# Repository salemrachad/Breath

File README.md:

# Breath
Breath is an interactive installation that explores the realms of mindfulness through emergent intelligence

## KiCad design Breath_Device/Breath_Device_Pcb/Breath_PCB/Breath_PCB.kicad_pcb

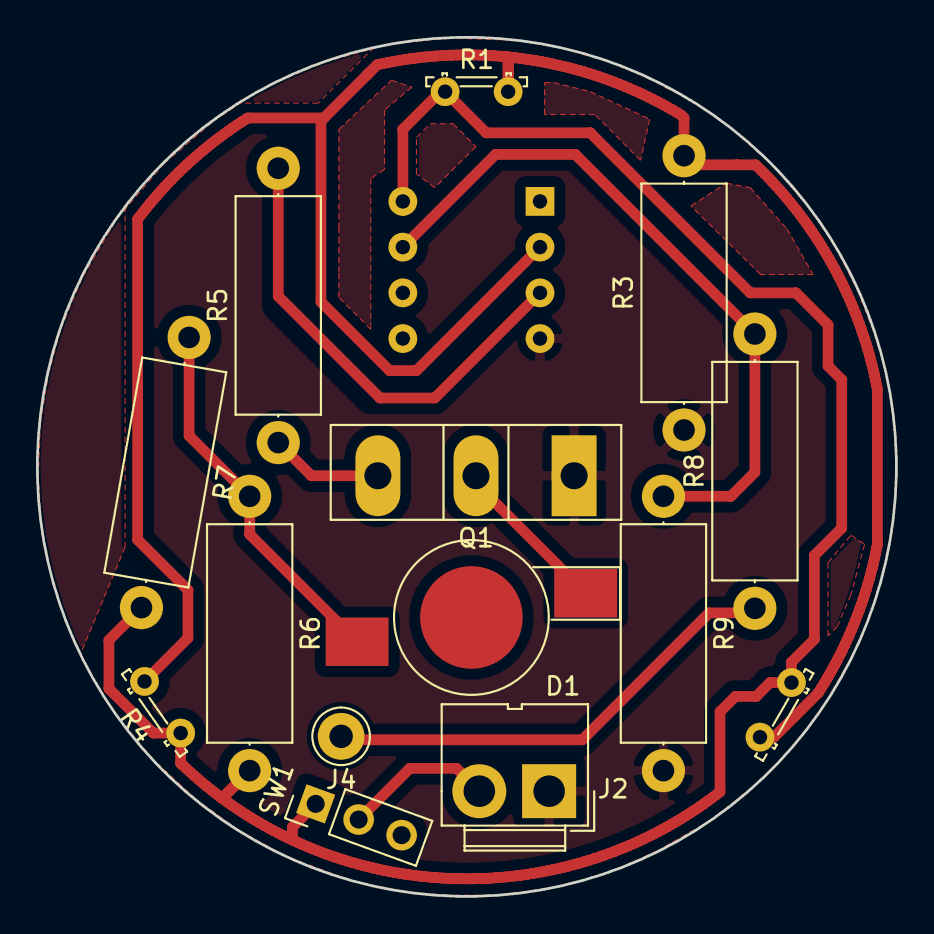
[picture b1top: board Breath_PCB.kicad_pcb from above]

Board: 2 copper layers, 47.7 x 47.7 mm, 15 parts (1 on the bottom side), 10 nets.

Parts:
D1: LED; LED_1W_3W_R8
J2: Conn_01x02_Female; JWT_A3963_1x02_P3.96mm_Vertical
J4: Conn_01x01_Male; Pin_D1.3mm_L11.0mm
Q1: BUK9M28-80EX; TO-247-3_Vertical
R1, R2, R4: R_PHOTO; R_LDR_5.2x5.2mm_P3.5mm_Horizontal
R3: 10kR; R_Axial_DIN0414_L11.9mm_D4.5mm_P15.24mm_Horizontal
R5, R8, R9: 1kR; R_Axial_DIN0414_L11.9mm_D4.5mm_P15.24mm_Horizontal
R6, R7: 10R; R_Axial_DIN0414_L11.9mm_D4.5mm_P15.24mm_Horizontal
SW1: SW_SPDT; PinHeader_1x03_P2.54mm_Vertical
U1: ATtiny85-20PU; DIP-8_W7.62mm

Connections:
+5V: R1.1, R2.1, R4.1, R6.2, R7.2, SW1.1, U1.8
GND: J2.1, Q1.1, R3.1, R9.2, U1.4
unnamed: D1.1, Q1.4
unnamed: D1.2, R6.1, R7.1
unnamed: J2.2, SW1.2
unnamed: J4.1, R8.1
unnamed: Q1.5, R5.1
unnamed: R1.2, R2.2, R3.2, R4.2, U1.2
unnamed: R5.2, U1.3
unnamed: R8.2, R9.1, U1.7

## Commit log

2020-06-29 arduino on vscode
2020-06-30 finally
2020-07-02 fixed structure
2020-07-02 Rename New Text Document.txt to Readme.txt
2020-07-02 txt namefiles change
2020-07-03 structure management
2020-07-03 Microphone tests
2020-07-07 stl files for geode shapes
2020-07-09 gcode
2020-07-09 Light tests on White pla material
2020-07-09 light test 2
2020-07-09 file name fix
2020-07-09 Implemented LDR
2020-07-12 no overlapping with light on click
2020-07-12 arraylist test
2020-07-14 Stl to obj
2020-07-16 Pcb_test_1
2020-07-16 resize
2020-07-18 particle system
2020-07-18 Noise
2020-07-20 noise experimentation
2020-07-20 new stl geode test2
2020-07-20 particle system update and some stls
2020-07-20 Processing minor modifications
2020-07-22 3d base and microphone test
2020-07-22 Attiny85 shield and testcode
2020-07-22 kicad
2020-07-24 code for attiny
2020-07-30 Pcb design and fabrication
2020-07-30 Stls and Processing Code
2020-08-01 more stl files
2020-08-02 new pcb design and filtered stl files
2020-08-03 stl,kicad,processing
2020-08-04 some processing shit
2020-08-06 stl and processing updates
2020-10-28 last file
